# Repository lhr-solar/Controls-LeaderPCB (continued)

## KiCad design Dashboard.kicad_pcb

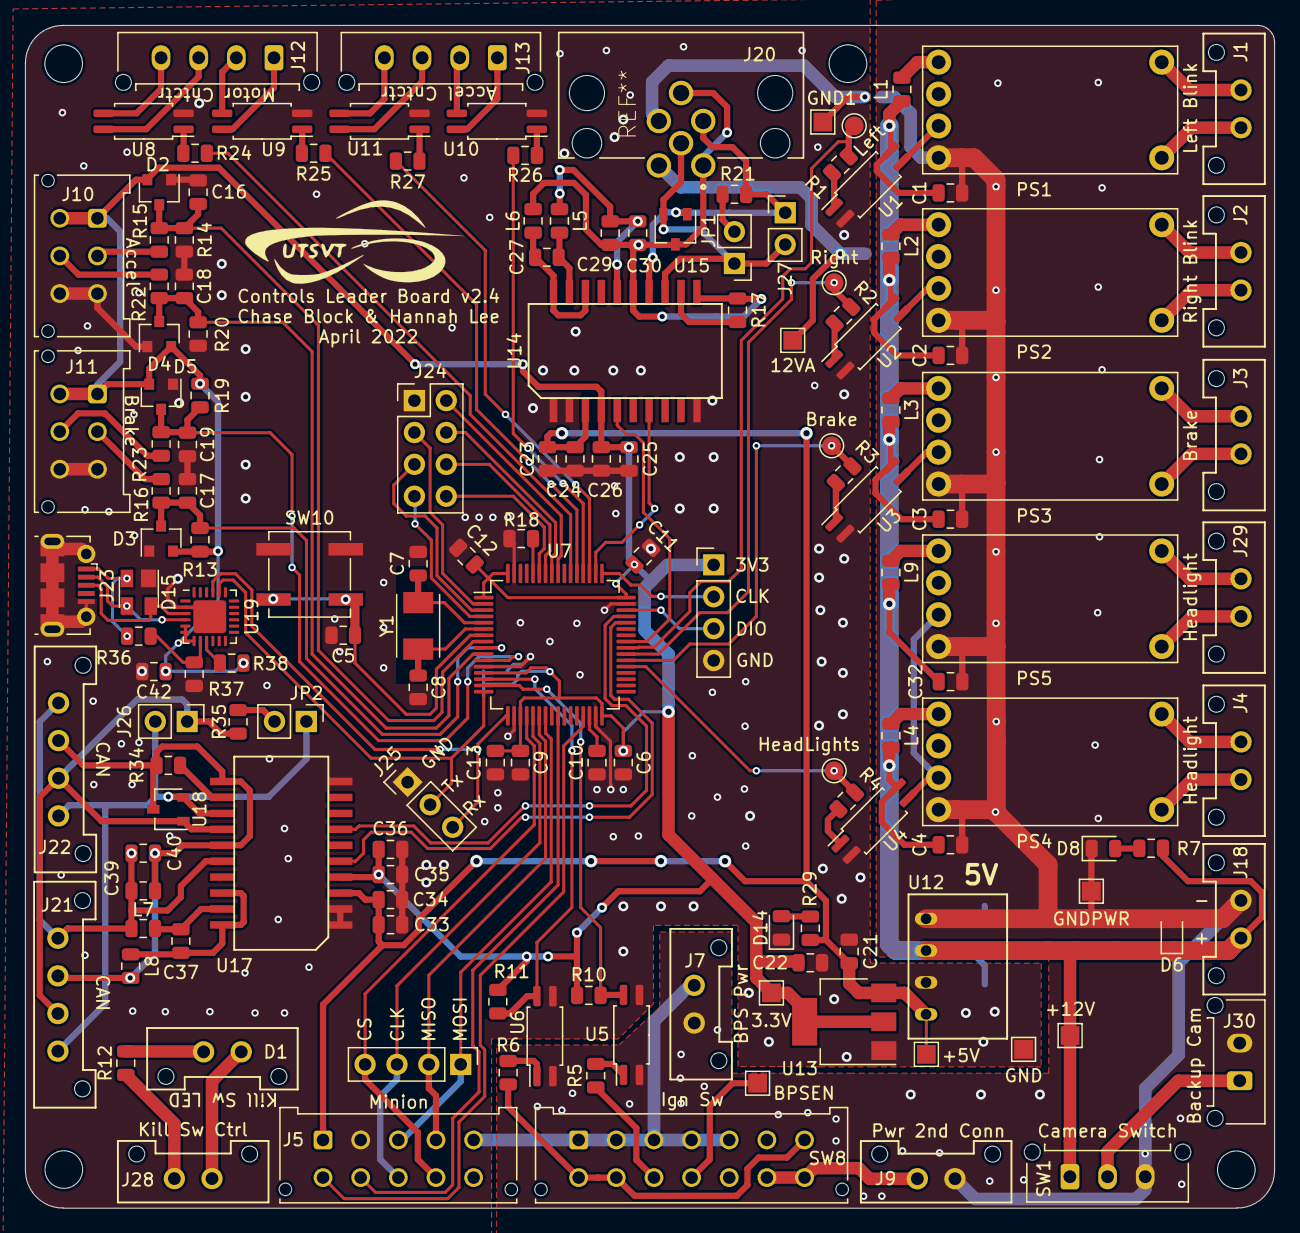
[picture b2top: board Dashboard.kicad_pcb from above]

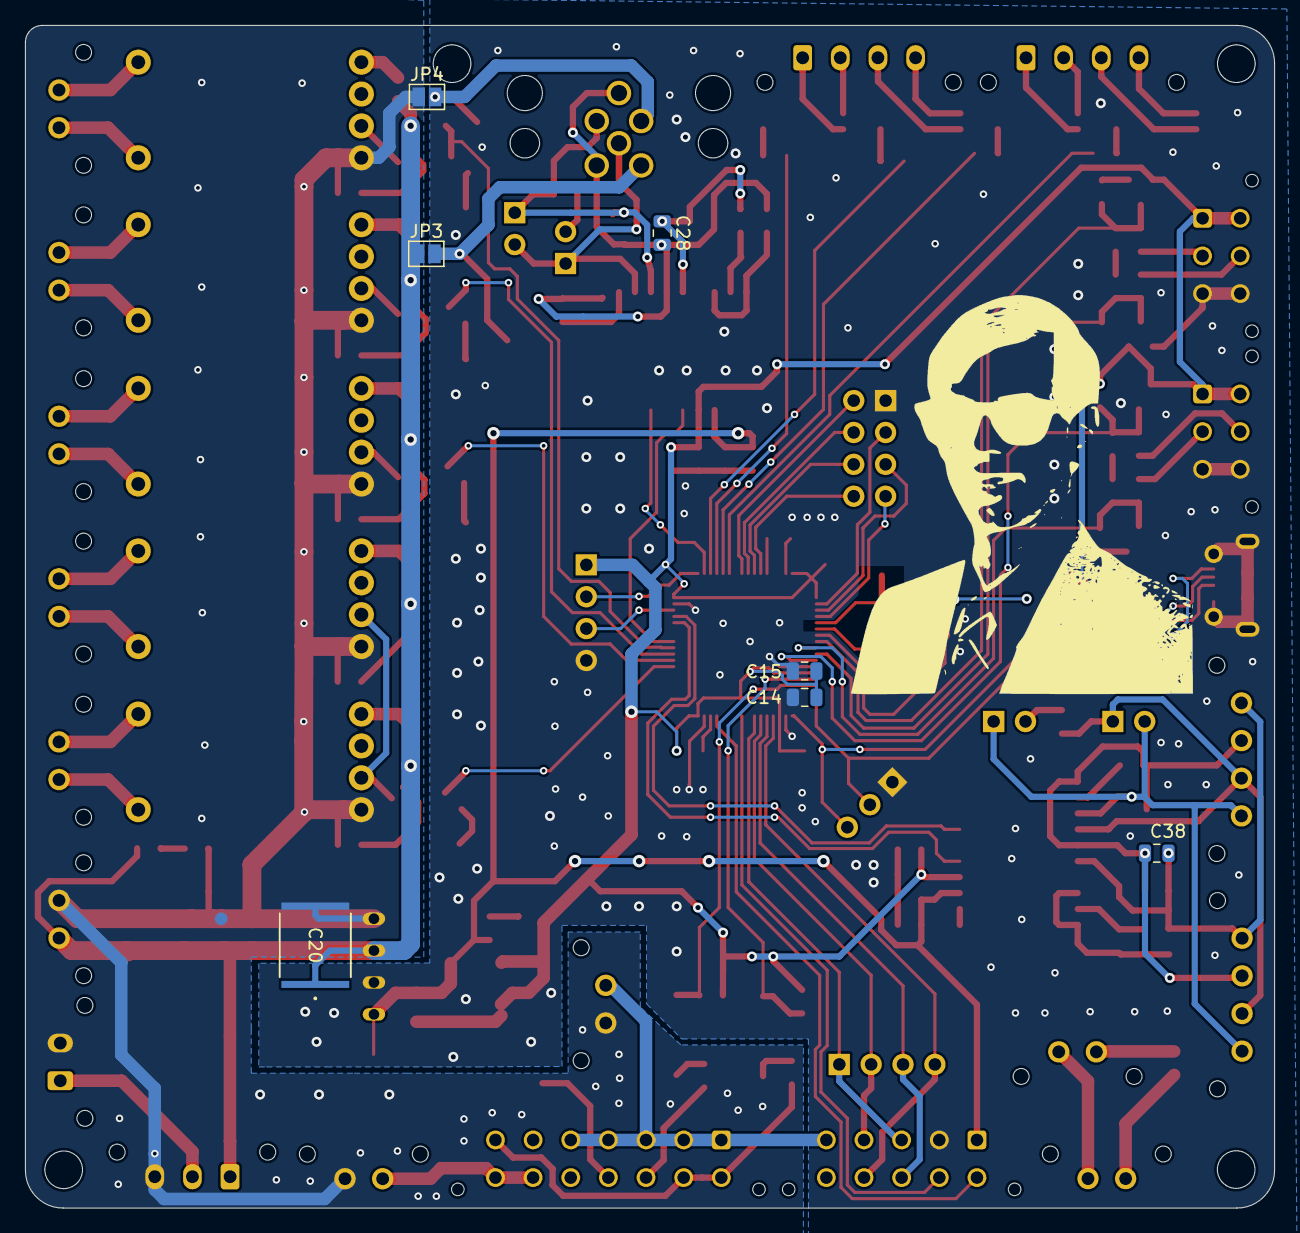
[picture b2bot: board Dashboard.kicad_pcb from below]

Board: 2 copper layers, 99.5 x 94.2 mm, 164 parts (9 on the bottom side), 120 nets.

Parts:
C1, C2, C3, C4, C32: 1u; C_0805_2012Metric
C5, C6, C9, C11, C12, C14: 100nF; C_0805_2012Metric
C7, C8: 12pF; C_0805_2012Metric
C10, C13, C41: 4.7uF; C_0805_2012Metric
C15: 1uF; C_0805_2012Metric
C16, C17, C18, C19, C24, C25, C29, C34, C35, C39, C42: 0.1uF; C_0805_2012Metric
C20: 10u; C_2220_5750Metric
C21, C22: 10u; C_0805_2012Metric
C23, C28, C33, C38: 10uF; C_0805_2012Metric
C26, C30, C36, C40: 0.01uF; C_0805_2012Metric
C27, C37: 0.22uF; C_0805_2012Metric
D1: KILL_SW_LED; Molex_MicroFit3.0_1x2xP3.00mm_PolarizingPeg_Vertical
D2, D3, D4, D5: BAS70-04; SOT-23
D6: TVS; D_SOD-323
D8, D14: PowerOn; LED_0805_2012Metric
D15: SP0503BAHT; SOT-143
H1, H2, H3, H4: MountingHole; MountingHole_3mm
J1: Left_Signal; Molex_MicroFit3.0_1x2xP3.00mm_PolarizingPeg_Vertical
J2: Right_Signal; Molex_MicroFit3.0_1x2xP3.00mm_PolarizingPeg_Vertical
J3: Brake Light; Molex_MicroFit3.0_1x2xP3.00mm_PolarizingPeg_Vertical
J4, J29: Headlight; Molex_MicroFit3.0_1x2xP3.00mm_PolarizingPeg_Vertical
J5: MinionConn; Molex_Micro-Fit_3.0_43045-1012_2x05_P3.00mm_Vertical
J6: SPI; PinHeader_1x04_P2.54mm_Vertical
J7: BPS_PWR_OUT; Molex_MicroFit3.0_1x2xP3.00mm_PolarizingPeg_Vertical
J8: SWD; PinHeader_1x04_P2.54mm_Vertical
J9: POW_2ND_CONN; Molex_MicroFit3.0_1x2xP3.00mm_PolarizingPeg_Vertical
J10, J11: Conn_02x03_Top_Bottom; Molex_Micro-Fit_3.0_43045-0612_2x03_P3.00mm_Vertical
J12, J13: Conn_01x04; Molex_Micro-Fit_3.0_43650-0415_1x04_P3.00mm_Vertical
J18: PowerConn; Molex_MicroFit3.0_1x2xP3.00mm_PolarizingPeg_Vertical
J20: MotorCANConnector; TE_4-2172079-2
J21: CAN_IN; Molex_MicroFit3.0_1x4xP3.00mm_PolarizingPeg_Vertical
J22: CAN_OUT; Molex_MicroFit3.0_1x4xP3.00mm_PolarizingPeg_Vertical
J23: USB_B_Micro; USB_Micro-B_Molex-105017-0001
J24: ExtraGPIO_Conn; PinHeader_2x04_P2.54mm_Vertical
J25: UART_TP; PinHeader_1x03_P2.54mm_Vertical
J26, J27: CAN_TP; PinHeader_1x02_P2.54mm_Vertical
J28: KILL_SW_IND; Molex_MicroFit3.0_1x2xP3.00mm_PolarizingPeg_Vertical
J30: Backup Camera; Molex_Micro-Fit_3.0_43650-0215_1x02_P3.00mm_Vertical
JP1, JP2: Termination Resistors; PinHeader_1x02_P2.54mm_Vertical
JP3, JP4: Jumper_2_Bridged; SolderJumper-2_P1.3mm_Open_Pad1.0x1.5mm
L1, L2, L3, L4, L9: 22u; L_0805_2012Metric
L5, L6, L7, L8: 2kH; L_0805_2012Metric
LOGO1: Dr. Hallock; Hallock_Image
LOGO2: UTSVT; UTSVT_Logo_Symbol
PS1, PS2, PS3, PS4, PS5: RCD-24
R1, R2, R3, R4: 105; R_0805_2012Metric
R5, R6: 510; R_0805_2012Metric
R7, R29: 1.5k; R_0805_2012Metric
R10, R11: 4.9k; R_0805_2012Metric
R12: 1.2k; R_0805_2012Metric
R13, R14, R19, R20: 5.1k; R_0805_2012Metric
R15, R16, R18, R22, R23: 10k; R_0805_2012Metric
R17, R34: 0; R_0805_2012Metric
R21, R35: 120; R_0805_2012Metric
R24, R25, R26, R27: 105R; R_0805_2012Metric
R36: 22.1k; R_0805_2012Metric
R37: 47.5k; R_0805_2012Metric
R38: 1k; R_0805_2012Metric
SW1: BACKUP_SW; Molex_Micro-Fit_3.0_43650-0315_1x03_P3.00mm_Vertical
SW8: SW_Rotary2x6; Molex_Micro-Fit_3.0_43045-1412_2x07_P3.00mm_Vertical
SW10: RESET; SW_SPST_B3SL-1002P
TP1: LEFT_BLINK; TestPoint_Pad_D1.5mm
TP2: +12V_TP; TestPoint_Pad_1.5x1.5mm
TP3: GNDPWR_TP; TestPoint_Pad_1.5x1.5mm
TP4: +5V_TP; TestPoint_Pad_1.5x1.5mm
TP5: GND_TP; TestPoint_Pad_1.5x1.5mm
TP6: +3.3V_TP; TestPoint_Pad_1.5x1.5mm
TP7: RIGHT_BLINK; TestPoint_Pad_D1.5mm
TP8: BK_LIGHT; TestPoint_Pad_D1.5mm
TP9: Headlight_PWR; TestPoint_Pad_D1.5mm
TP10: POWER; TestPoint_Pad_1.5x1.5mm
TP13: +12VA_TP; TestPoint_Pad_1.5x1.5mm
TP14: GND1_TP; TestPoint_Pad_1.5x1.5mm
U1, U2, U3, U4, U5, U6, U8, U9, U10, U11: EL3H7; SOP-4_4.4x2.6mm_P1.27mm
U7: STM32F413RHTx; LQFP-64_10x10mm_P0.5mm
U12: RI3-1205S; RI3_DC_Converter
U13: NCP1117-3.3_SOT223; SOT-223-3_TabPin2
U14, U17: ADM3055E; SOIC-20W_7.5x15.4mm_Pitch1.27mm
U15, U18: CDSOT23-T24CAN; SOT-23W
U19: CP2102N-A01-GQFN24; QFN-24-1EP_4x4mm_P0.5mm_EP2.6x2.6mm
Y1: Crystal; Crystal_SMD_TXC_7A-2Pin_5x3.2mm

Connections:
+3V3: C6.1, C9.1, C11.1, C12.1, C13.1, C14.1, C15.1, C22.1, C25.1, C26.1, C35.1, C36.1, C41.1, C42.1, D2.2, D3.2, D4.2, D5.2, J8.1, J10.1, J10.4, J11.1, J11.4, R10.1, R11.1, R13.1, R19.1, R38.1, TP6.1, U7.1 (VBAT), U7.13 (VDDA), U7.19 (VDD), U7.32 (VDD), U7.48 (VDD), U7.64 (VDD), U13.2 (VO), U14.4 (V_IO), U17.4 (V_IO), U19.5 (VIO), U19.6 (VDD), U19.7 (REGIN)
+5V: C21.1, C23.1, C24.1, C33.1, C34.1, J5.1, R29.1, TP4.1, U12.4 (+Vout), U13.3 (VI), U14.3 (V_In), U17.3 (V_In)
+12V: C1.2, C2.2, C3.2, C4.2, C20.1, C32.2, D6.1 (K), J18.1, JP3.1 (A), L1.2, L2.2, L3.2, L4.2, L9.2, R7.1, SW1.1 (A), TP2.1, U1.4, U2.4, U3.4, U4.4, U12.2 (+Vin)
+12VA: J20.2 (+12V), JP3.2 (B), TP13.1
/A_CNCTR: R26.2, U7.52 (PC11)
/A_PRCHG: R27.2, U7.51 (PC10)
/Accel_Pot: C16.1, D2.3, R14.1, R15.2, U7.8 (PC0)
/Accel_Pot2: C18.1, D4.3, R20.1, R22.2, U7.10 (PC2)
/BK_LIGHT: R3.2, TP8.1, U7.38 (PC7)
/BPS_PWR: J5.5, J7.1, SW8.1, SW8.2, SW8.3, SW8.4, SW8.5
/Brake_Pot: C17.1, D3.3, R13.2, R16.2, U7.9 (PC1)
/Brake_Pot2: C19.1, D5.3, R19.2, R23.2, U7.11 (PC3)
/CAN_Rx: U7.44 (PA11), U17.5 (RX)
/CAN_Tx: U7.45 (PA12), U17.7 (TX)
/CLK: J5.8, J6.3, U7.21 (PA5)
/CS: J5.9, J6.4, U7.20 (PA4)
/Car_CAN/CAN_H: J21.3, J22.3, J26.1, R35.2, U17.14 (CAN_H), U18.1 (CAN_H)
/Car_CAN/CAN_L: J21.4, J22.4, J26.2, JP2.1, U17.13 (CAN_L), U18.2 (CAN_L)
/Car_CAN/RSlope: R34.1, U17.12 (RS)
/Car_CAN/TERM_H: JP2.2, R35.1
/Headlight_ON: R4.2, TP9.1, U7.37 (PC6)
/IG1: R10.2, U5.4, U7.15 (PA1)
/IG2: R11.2, U6.4, U7.14 (PA0)
/LEFT_BLINK: R1.2, TP1.1, U7.40 (PC9)
/MISO: J5.4, J6.2, U7.22 (PA6)
/MOSI: J5.3, J6.1, U7.23 (PA7)
/M_CNCTR: R25.2, U7.53 (PC12)
/M_PRCHG: R24.2, U7.54 (PD2)
/MotorCAN_Rx: U7.41 (PA8), U14.5 (RX)
/MotorCAN_Tx: U7.50 (PA15), U14.7 (TX)
/Motor_CAN/CAN_H: J20.4 (CAN_H), J27.1, R21.2, U14.14 (CAN_H), U15.1 (CAN_H)
/Motor_CAN/CAN_L: J20.5 (CAN_L), J27.2, JP1.1, U14.13 (CAN_L), U15.2 (CAN_L)
/Motor_CAN/RSlope: R17.1, U14.12 (RS)
/Motor_CAN/TERM_H: JP1.2, R21.1
/NRST: C5.1, SW10.2 (B), U7.7 (NRST)
/PB4: J24.2, U7.56 (PB4)
/PB5: J24.4, U7.57 (PB5)
/PB6: J24.6, U7.58 (PB6)
/PB7: J24.8, U7.59 (PB7)
/PC13: J24.3, U7.2 (PC13)
/PC14: J24.5, U7.3 (PC14)
/PC15: J24.7, U7.4 (PC15)
/RIGHT_BLINK: R2.2, TP7.1, U7.39 (PC8)
/SWCLK: J8.2, U7.49 (PA14)
/SWDIO: J8.3, U7.46 (PA13)
/UART2_Rx: J25.3, U7.17 (PA3), U19.21 (TXD)
/UART2_Tx: J25.2, U7.16 (PA2), U19.20 (RXD)
/UART3_Rx: J5.7, U7.25 (PC5)
/UART3_Tx: J5.6, U7.29 (PB10)
GND: C5.2, C6.2, C7.2, C8.2, C9.2, C10.1, C11.2, C12.2, C13.2, C14.2, C15.2, C16.2, C17.2, C18.2, C19.2, C21.2, C22.2, C23.2, C24.2, C25.2, C26.2, C33.2, C34.2, C35.2, C36.2, C41.2, C42.2, D2.1, D3.1, D4.1, D5.1, D14.1 (K), D15.1 (A), J5.2, J8.4, J10.3, J10.6, J11.3, J11.6, J23.5 (GND), J23.6 (Shield), J24.1, J25.1, R14.2, R18.2, R20.2, R37.2, SW10.1 (A), TP5.1, U1.2, U2.2, U3.2, U4.2, U5.3, U6.3, U7.12 (VSSA), U7.18 (VSS), U7.31 (VSS), U7.47 (VSS), U7.63 (VSS), U8.2, U9.2, U10.2, U11.2, U12.3 (-Vout), U13.1 (GND), U14.1 (GND_In), U14.2 (GND_In), U14.10 (GND_In), U17.1 (GND_In), U17.2 (GND_In), U17.10 (GND_In), U19.2 (GND), U19.25 (GND)
GND1: J20.3 (GND), JP4.2 (B), TP14.1
GNDPWR: C1.1, C2.1, C3.1, C4.1, C20.2, C32.1, D6.2 (A), D8.1 (K), J7.2, J9.2, J18.2, J30.2, JP4.1 (A), PS1.4 (GND), PS2.4 (GND), PS3.4 (GND), PS4.4 (GND), PS5.4 (GND), SW1.3 (C), TP3.1, U5.2, U6.2, U12.1 (-Vin)
unnamed: C7.1, U7.5 (PH0), Y1.2
unnamed: C8.1, U7.6 (PH1), Y1.1
unnamed: C10.2, U7.30 (VCAP_1)
unnamed: C27.1, L5.2, U14.19 (V_ISO_Out)
unnamed: C27.2, L6.2, U14.18 (GND_ISO_Out), U14.20 (GND_ISO_Out)
unnamed: C28.1, C29.1, C30.1, L5.1, U14.16 (V_ISO_In)
unnamed: C28.2, C29.2, C30.2, J20.1 (Shield_GND), J20.S1 (SHIELD), L6.1, R17.2, U14.11 (GND_ISO_In), U14.15 (GND_ISO_In), U15.3 (GND)
unnamed: C37.1, L7.2, U17.19 (V_ISO_Out)
unnamed: C37.2, L8.2, U17.18 (GND_ISO_Out), U17.20 (GND_ISO_Out)
unnamed: C38.1, C39.1, C40.1, J21.1, J22.1, L7.1, U17.16 (V_ISO_In)
unnamed: C38.2, C39.2, C40.2, J21.2, J22.2, L8.1, R34.2, U17.11 (GND_ISO_In), U17.15 (GND_ISO_In), U18.3 (GND)
unnamed: D1.1 (K), J28.2
unnamed: D1.2 (A), R12.2
unnamed: D8.2 (A), R7.2
unnamed: D14.2 (A), R29.2
unnamed: D15.2 (K), J23.1 (VBUS), R36.2
unnamed: D15.3 (K), J23.2 (D-), U19.4 (D-)
unnamed: D15.4 (K), J23.3 (D+), U19.3 (D+)
unnamed: J1.1, PS1.5 (-Vout)
unnamed: J1.2, PS1.6 (+Vout)
unnamed: J2.1, PS2.5 (-Vout)
unnamed: J2.2, PS2.6 (+Vout)
unnamed: J3.1, PS3.5 (-Vout)
unnamed: J3.2, PS3.6 (+Vout)
unnamed: J4.1, PS4.5 (-Vout)
unnamed: J4.2, PS4.6 (+Vout)
unnamed: J9.1, SW8.13, SW8.14
unnamed: J28.1, R12.1
unnamed: J29.1, PS5.5 (-Vout)
unnamed: J29.2, PS5.6 (+Vout)
unnamed: J30.1, SW1.2 (B)
unnamed: L1.1, PS1.1 (+Vin)
unnamed: L2.1, PS2.1 (+Vin)
unnamed: L3.1, PS3.1 (+Vin)
unnamed: L4.1, PS4.1 (+Vin)
unnamed: L9.1, PS5.1 (+Vin)
unnamed: PS1.3 (PWM), U1.3
unnamed: PS2.3 (PWM), U2.3
unnamed: PS3.3 (PWM), U3.3
unnamed: PS4.3 (PWM), PS5.3 (PWM), U4.3
unnamed: R1.1, U1.1
unnamed: R2.1, U2.1
unnamed: R3.1, U3.1
unnamed: R4.1, U4.1
unnamed: R5.1, SW8.10
unnamed: R5.2, U5.1
unnamed: R6.1, SW8.7, SW8.8, SW8.9
unnamed: R6.2, U6.1
unnamed: J10.2, R15.1
unnamed: J11.2, R16.1
unnamed: R18.1, U7.60 (BOOT0)
unnamed: J10.5, R22.1
unnamed: J11.5, R23.1
unnamed: R24.1, U8.1
unnamed: R25.1, U9.1
unnamed: R26.1, U10.1
unnamed: R27.1, U11.1
unnamed: R36.1, R37.1, U19.8 (VBUS)
unnamed: R38.2, U19.9 (~RSTb)
unnamed: SW8.11, TP10.1
unnamed: J12.4, U8.3
unnamed: J12.3, U8.4
unnamed: J12.2, U9.3
unnamed: J12.1, U9.4
unnamed: J13.2, U10.3
unnamed: J13.1, U10.4
unnamed: J13.4, U11.3
unnamed: J13.3, U11.4

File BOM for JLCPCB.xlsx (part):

Comment |  |  | Designator |  |  |  | Footprint |  |  |  |  |  |  | JLCPCB Part # P/N |  |  | Stock in jlc
1u |  |  | C1 |  |  |  | Capacitor_SMD:C_0805_2012Metric |  |  |  |  |  |  | C28323 |  |  | 647623
1u |  |  | C2 |  |  |  | Capacitor_SMD:C_0805_2012Metric |  |  |  |  |  |  | C28323 |  |  | 647623
1u |  |  | C3 |  |  |  | Capacitor_SMD:C_0805_2012Metric |  |  |  |  |  |  | C28323 |  |  | 647623
1u |  |  | C4 |  |  |  | Capacitor_SMD:C_0805_2012Metric |  |  |  |  |  |  | C28323 |  |  | 647623
1u |  |  | C32 |  |  |  | Capacitor_SMD:C_0805_2012Metric |  |  |  |  |  |  | C28323 |  |  | 647623
100nF |  |  | C5 |  |  |  | Capacitor_SMD:C_0805_2012Metric |  |  |  |  |  |  | C49678 |  |  | 6507420
100nF |  |  | C6 |  |  |  | Capacitor_SMD:C_0805_2012Metric |  |  |  |  |  |  | C49678 |  |  | 6507420
100nF |  |  | C9 |  |  |  | Capacitor_SMD:C_0805_2012Metric |  |  |  |  |  |  | C49678 |  |  | 6507420
100nF |  |  | C11 |  |  |  | Capacitor_SMD:C_0805_2012Metric |  |  |  |  |  |  | C49678 |  |  | 6507420
100nF |  |  | C12 |  |  |  | Capacitor_SMD:C_0805_2012Metric |  |  |  |  |  |  | C49678 |  |  | 6507420
100nF |  |  | C16 |  |  |  | Capacitor_SMD:C_0805_2012Metric |  |  |  |  |  |  | C49678 |  |  | 6507420
100nF |  |  | C17 |  |  |  | Capacitor_SMD:C_0805_2012Metric |  |  |  |  |  |  | C49678 |  |  | 6507420
100nF |  |  | C18 |  |  |  | Capacitor_SMD:C_0805_2012Metric |  |  |  |  |  |  | C49678 |  |  | 6507420
100nF |  |  | C19 |  |  |  | Capacitor_SMD:C_0805_2012Metric |  |  |  |  |  |  | C49678 |  |  | 6507420
100nF |  |  | C24 |  |  |  | Capacitor_SMD:C_0805_2012Metric |  |  |  |  |  |  | C49678 |  |  | 6507420
100nF |  |  | C25 |  |  |  | Capacitor_SMD:C_0805_2012Metric |  |  |  |  |  |  | C49678 |  |  | 6507420
100nF |  |  | C29 |  |  |  | Capacitor_SMD:C_0805_2012Metric |  |  |  |  |  |  | C49678 |  |  | 6507420
100nF |  |  | C34 |  |  |  | Capacitor_SMD:C_0805_2012Metric |  |  |  |  |  |  | C49678 |  |  | 6507420
100nF |  |  | C35 |  |  |  | Capacitor_SMD:C_0805_2012Metric |  |  |  |  |  |  | C49678 |  |  | 6507420
100nF |  |  | C39 |  |  |  | Capacitor_SMD:C_0805_2012Metric |  |  |  |  |  |  | C49678 |  |  | 6507420
100nF |  |  | C42 |  |  |  | Capacitor_SMD:C_0805_2012Metric |  |  |  |  |  |  | C49678 |  |  | 6507420
12pF |  |  | C7 |  |  |  | Capacitor_SMD:C_0805_2012Metric |  |  |  |  |  |  | C376863 |  |  | 3913
12pF |  |  | C8 |  |  |  | Capacitor_SMD:C_0805_2012Metric |  |  |  |  |  |  | C376863 |  |  | 3913
4.7uF |  |  | C10 |  |  |  | Capacitor_SMD:C_0805_2012Metric |  |  |  |  |  |  | C1779 |  |  | 2094551
4.7uF |  |  | C13 |  |  |  | Capacitor_SMD:C_0805_2012Metric |  |  |  |  |  |  | C1779 |  |  | 2094551
4.7uF |  |  | C41 |  |  |  | Capacitor_SMD:C_0805_2012Metric |  |  |  |  |  |  | C1779 |  |  | 2094551
10u |  |  | C20 |  |  |  | Capacitor_SMD:C_0805_2012Metric |  |  |  |  |  |  | C15850 |  |  | 5148770
10u |  |  | C21 |  |  |  | Capacitor_SMD:C_0805_2012Metric |  |  |  |  |  |  | C15850 |  |  | 5148770
10u |  |  | C22 |  |  |  | Capacitor_SMD:C_0805_2012Metric |  |  |  |  |  |  | C15850 |  |  | 5148770
10u |  |  | C23 |  |  |  | Capacitor_SMD:C_0805_2012Metric |  |  |  |  |  |  | C15850 |  |  | 5148770
10u |  |  | C28 |  |  |  | Capacitor_SMD:C_0805_2012Metric |  |  |  |  |  |  | C15850 |  |  | 5148770
10u |  |  | C33 |  |  |  | Capacitor_SMD:C_0805_2012Metric |  |  |  |  |  |  | C15850 |  |  | 5148770
10u |  |  | C38 |  |  |  | Capacitor_SMD:C_0805_2012Metric |  |  |  |  |  |  | C15850 |  |  | 5148770
0.01uF |  |  | C26 |  |  |  | Capacitor_SMD:C_0805_2012Metric |  |  |  |  |  |  | C1710 |  |  | 518880
0.01uF |  |  | C30 |  |  |  | Capacitor_SMD:C_0805_2012Metric |  |  |  |  |  |  | C1710 |  |  | 518880
0.01uF |  |  | C36 |  |  |  | Capacitor_SMD:C_0805_2012Metric |  |  |  |  |  |  | C1710 |  |  | 518880
0.01uF |  |  | C40 |  |  |  | Capacitor_SMD:C_0805_2012Metric |  |  |  |  |  |  | C1710 |  |  | 518880
0.22uF |  |  | C27 |  |  |  | Capacitor_SMD:C_0805_2012Metric |  |  |  |  |  |  | C5378 |  |  | 135203
0.22uF |  |  | C37 |  |  |  | Capacitor_SMD:C_0805_2012Metric |  |  |  |  |  |  | C5378 |  |  | 135203
BAS70-04 |  |  | D2 |  |  |  | Package_TO_SOT_SMD:SOT-23 |  |  |  |  |  |  | C5184402 |  |  | 24530
BAS70-04 |  |  | D3 |  |  |  | Package_TO_SOT_SMD:SOT-23 |  |  |  |  |  |  | C5184402 |  |  | 24530
BAS70-04 |  |  | D4 |  |  |  | Package_TO_SOT_SMD:SOT-23 |  |  |  |  |  |  | C5184402 |  |  | 24530
BAS70-04 |  |  | D5 |  |  |  | Package_TO_SOT_SMD:SOT-23 |  |  |  |  |  |  | C5184402 |  |  | 24530
TVS |  |  | D6 |  |  |  | Diode_SMD:D_SOD-323 |  |  |  |  |  |  | C5190176 |  |  | 833
PowerOn |  |  | D8 |  |  |  | LED_SMD:LED_0805_2012Metric |  |  |  |  |  |  | C5366381 |  |  | 3139
PowerOn |  |  | D14 |  |  |  | LED_SMD:LED_0805_2012Metric |  |  |  |  |  |  | C5366381 |  |  | 3139
SP0503BAHT |  |  | D15 |  |  |  | Package_TO_SOT_SMD:SOT-143 |  |  |  |  |  |  | C3040626 |  |  | 120289
110 |  |  | R1 |  |  |  | Resistor_SMD:R_0805_2012Metric |  |  |  |  |  |  | C2933517 |  |  | 844
110 |  |  | R2 |  |  |  | Resistor_SMD:R_0805_2012Metric |  |  |  |  |  |  | C2933517 |  |  | 844
110 |  |  | R3 |  |  |  | Resistor_SMD:R_0805_2012Metric |  |  |  |  |  |  | C2933517 |  |  | 844
110 |  |  | R4 |  |  |  | Resistor_SMD:R_0805_2012Metric |  |  |  |  |  |  | C2933517 |  |  | 844
110 |  |  | R24 |  |  |  | Resistor_SMD:R_0805_2012Metric |  |  |  |  |  |  | C2933517 |  |  | 844
110 |  |  | R25 |  |  |  | Resistor_SMD:R_0805_2012Metric |  |  |  |  |  |  | C2933517 |  |  | 844
110 |  |  | R26 |  |  |  | Resistor_SMD:R_0805_2012Metric |  |  |  |  |  |  | C2933517 |  |  | 844
110 |  |  | R27 |  |  |  | Resistor_SMD:R_0805_2012Metric |  |  |  |  |  |  | C2933517 |  |  | 844
510 |  |  | R5 |  |  |  | Resistor_SMD:R_0805_2012Metric |  |  |  |  |  |  | C2828857 |  |  | 964
510 |  |  | R6 |  |  |  | Resistor_SMD:R_0805_2012Metric |  |  |  |  |  |  | C2828857 |  |  | 964
1.5k |  |  | R7 |  |  |  | Resistor_SMD:R_0805_2012Metric |  |  |  |  |  |  | C4310 |  |  | 436191
1.5k |  |  | R29 |  |  |  | Resistor_SMD:R_0805_2012Metric |  |  |  |  |  |  | C4310 |  |  | 436191
5k |  |  | R10 |  |  |  | Resistor_SMD:R_0805_2012Metric |  |  |  |  |  |  | C2828700 |  |  | 3316
5k |  |  | R11 |  |  |  | Resistor_SMD:R_0805_2012Metric |  |  |  |  |  |  | C2828700 |  |  | 3316
5k |  |  | R13 |  |  |  | Resistor_SMD:R_0805_2012Metric |  |  |  |  |  |  | C2828700 |  |  | 3316
5k |  |  | R14 |  |  |  | Resistor_SMD:R_0805_2012Metric |  |  |  |  |  |  | C2828700 |  |  | 3316
5k |  |  | R19 |  |  |  | Resistor_SMD:R_0805_2012Metric |  |  |  |  |  |  | C2828700 |  |  | 3316
5k |  |  | R20 |  |  |  | Resistor_SMD:R_0805_2012Metric |  |  |  |  |  |  | C2828700 |  |  | 3316
1.2k |  |  | R12 |  |  |  | Resistor_SMD:R_0805_2012Metric |  |  |  |  |  |  | C17379 |  |  | 163751
10k |  |  | R15 |  |  |  | Resistor_SMD:R_0805_2012Metric |  |  |  |  |  |  | C17414 |  |  | 18834045
10k |  |  | R16 |  |  |  | Resistor_SMD:R_0805_2012Metric |  |  |  |  |  |  | C17414 |  |  | 18834045
10k |  |  | R18 |  |  |  | Resistor_SMD:R_0805_2012Metric |  |  |  |  |  |  | C17414 |  |  | 18834045
10k |  |  | R22 |  |  |  | Resistor_SMD:R_0805_2012Metric |  |  |  |  |  |  | C17414 |  |  | 18834045
10k |  |  | R23 |  |  |  | Resistor_SMD:R_0805_2012Metric |  |  |  |  |  |  | C17414 |  |  | 18834045
0 |  |  | R17 |  |  |  | Resistor_SMD:R_0805_2012Metric |  |  |  |  |  |  | C17477 |  |  | 1157685
0 |  |  | R34 |  |  |  | Resistor_SMD:R_0805_2012Metric |  |  |  |  |  |  | C17477 |  |  | 1157685
120 |  |  | R21 |  |  |  | Resistor_SMD:R_0805_2012Metric |  |  |  |  |  |  | C17437 |  |  | 303844
120 |  |  | R35 |  |  |  | Resistor_SMD:R_0805_2012Metric |  |  |  |  |  |  | C17437 |  |  | 303844
22.1k |  |  | R36 |  |  |  | Resistor_SMD:R_0805_2012Metric |  |  |  |  |  |  | C17552 |  |  | 50
47.5k |  |  | R37 |  |  |  | Resistor_SMD:R_0805_2012Metric |  |  |  |  |  |  | C26011 |  |  | 2177
1k |  |  | R38 |  |  |  | Resistor_SMD:R_0805_2012Metric |  |  |  |  |  |  | C17513 |  |  | 9841243
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
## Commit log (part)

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2020-08-02 Set up for own repository
2020-08-08 Updates submodule commit ID
2020-08-08 Updates dashboard project to most recent version
2020-08-11 Adds files to a new branch
2020-09-12 Updates common
2020-09-12 Edits schematic to make turn lights software controlled
2020-09-12 Updates PCB to add changes from the schematic
2020-09-12 Updates common submodule
2020-09-19 Organizes the schematic into hierarchical sheets
2020-09-19 Generates netlist and updates PCB components
2020-09-27 Adds components for the shift register and lays out modularized components
2020-09-27 Lays out PCB for Controls leader board
2020-10-01 Adds SPI header to test
2020-10-01 Makes all traces .25 mm
2020-10-03 Labels sections and fixes DRC errors
2020-10-03 Adds QuAC
2020-10-03 Adds labels to some connectors and edits layout to meet 0,2mm pad to trace clearance
2020-10-03 Finishes label and redesigns emergency switch/error light circuitry
2020-10-03 Adds connector for power secondary board
2020-10-09 Makes the 12V and GNDPWR traces bigger
2020-10-09 Extends the GND plane to under the potentiometers
2020-10-09 Creates and then removes Gerbers
2020-10-10 Add STEP file
2020-12-12 Creates pdf of schematic
2020-12-19 Adds BPSPWR as a connection to the minion board and then fixes labels
2021-01-10 Changes display power to 5V, puts fault LED on back, and adds gerbers
2021-01-23 Adds gerbers
2021-01-23 Updates Controls Leader PCB
2021-02-06 3D models and resized rotary switch
2021-02-06 Cleans up folder and updates gerbers
2021-10-02 USB Tx/Rx, Crystal Keepout, 12V Separation, Can2-Can3, Motor CAN bus labels, Power Input Protection Circuitry
2021-10-03 Connects pots to ADC pins and removes JTAG connections
2021-10-03 Flips exterior lights polarity on the connectors
2021-10-04 Updates gerbers and version number
2021-11-06 removes the isp
2021-11-06 removes isp
2021-11-14 Changes the layout of the board, adds resistors for ignition switch, and gives motar can isolated +12v, still need to change resistor value for the isolated +12v(didnt remember how to find the value)
2021-11-16 Cleans up some of the traces in the power section
2021-12-07 Updates gerbers and new controls leader
2022-02-21 Redo the board layout to be more compact.
    IMPORTANT: as of this moment, this is only a proposal for
    a new design, and the team has *not* determined whether
    this is necessary.
    This addresses some issues that I have had with the design
    of the Controls Leader board:
    - It is too bulky, and would be difficult to mount
2022-04-02 Remove 12V isolator, swap CAN connector pins, etc.
2022-04-02 Release v2.4 and gerbers
2023-10-13 Initialized Controls Daughter PCB
2023-10-13 Removed .lck file
2023-10-13 updated gitignore
2023-10-13 added UTSVT submodule
2023-10-14 changed resistor values, updated footprints
2023-10-21 Added drived fan circuitry
2023-10-21 Added resistor to fan isolator, fixed ERC errors and warnings
2023-10-21 added version history text
2023-10-21 changed labels for some connectors
2023-10-28 renamed root directory
2023-10-28 fixed renaming, no longer has duplicated project
2023-10-28 lower power optocouplers now used for lights and fans, updated version history
2023-10-28 changed version history
2023-11-04 Added flyback diodes to fan connectors
2023-11-04 Removed ignition switch connection and redid ignition signals
2023-11-04 Layed out SOM boot-hat connections
2023-11-04 Removed neutral section's debouncing circuitry and connections
2023-11-04 Added test points
2023-11-04 Adjusted & added footprints, several minor changes
2023-11-04 Changed optocoupler resistor values, updated Mouser PNs
2023-11-04 Uploaded image for ReadME
2023-11-04 Changed image file name
2023-11-04 Updated ReadME image
2023-12-02 Switch ignition switch signal's resistor from pull-up to pull-down
2023-12-02 Added I2C GPIO expander to reduce GPIO pins from LeaderSOM and replace 555 timer circuit. Adjusted ignition switch signals.
2024-01-07 Added debouncing, bypass caps, pull up and down resistors, and current limiting resistors. Removed some TPs.
2024-01-17 Organized schematic, removed fan MOSFET
2024-01-17 assigned footprints
2024-01-17 organized schematic, changed resistor values, moved ignition signals to IC
2024-01-17 added second fan FET back
2024-01-18 fixed library issues
2024-01-18 Organized schematic, added reset function to extender, changed footprints
2024-01-20 added notes section to bottom of sheets
2024-01-20 renamed Dash to Controls-Leader
2024-01-20 Added to notes and changed resistor values
2024-01-20 renamed Dash to Controls-Leader (#22)
    * renamed Dash to Controls-Leader
    * :)
2024-04-06 added jlc bom assembly excel file
2024-04-13 ignore .lck files and deleted lck files
2024-04-13 added cpl file (positions.csv), updated BOM excel sheet, turned gerbers into zip file
2024-04-13 moved positions out of a separate folder
2024-04-13 updated resistor parts (510 and 5.1k to 5k)
2024-04-13 rename excel sheet
2024-04-17 updated positions.csv
2024-06-05 fixed BOM
2024-06-05 fixed gitignore
2024-06-05 ahhhhhhhhhhhhhhhhhhhhhhhhhhhhhhhhhhhhhhhhhhhhhhhhhhhhhhhhhhhhhhhhhhhhhhhhhhhhhhhhhhhhhhhhhhhhhhhhhhhhhhhhhhhhhhhhhhhhhhhhhhhhhhhhhhhhhhhhhhhhhhhhhhhhhhhhhhhhhhhhhhhhhhhhh
2024-09-14 Schematic notations for rework changes
2024-09-21 Updated schematic in accordance to previous weeks annotated changes
2024-09-28 Added .lck files to .gitignore.
2024-09-28 Renamed Clk to PA5, removed CAN_TX/RX test points, deleted other .lck file and #auto_saved_files# (hopefully this does not break anything.
2024-09-28 Changed testpoints to pin headers.
2024-10-05 removed camera, fixed connectors, and changed status LEDS
2024-10-18 Added back lights + drivers + timer for all blinkers and brake lights
2024-10-19 Fuse added for motorCAN 12V
2024-10-26 Renamed local net labels to be different from hierarchical ones in the MinionBrdInterface so that they aren't connected. Changed Regen input to BPS Hazard light since we aren't using regen but will b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
2024-10-27 Flipped optoisolators, changed resistor values, added second connector to motor can and disconnected shield pins for now since I haven't seen them used (will chack against old version to see what the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
2024-10-27 Changed names and added power flags until KiCAD ERC was satisfied. Hopefully this did not involve doing anything that wasn't supposed to be done.
2024-10-27 Added UTSVT libraries to the gitignore.
2024-10-27 Added footprints. I think this is everything except the fuse.
2024-11-01 Fuse footprint added and blinker changed to software
2024-11-08 Started cleaning some comments, changed EL3H7 data sheet link, removed extra motor CAN connector and changed original one to match (I think) motor controller connector, removed extra mounting holes, 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
2024-11-08 Updated contactor pins.
2024-11-09 added circuitry for limit switch brake, added mosfet to drive LEDs, cleaned up legacy comments, updated resistor values for LEDs
2024-11-09 fixed some footprints and part numbers
2024-11-10 Added/checked datasheet links/part numbers, deleted accel_pot2 and brake_pot2 hierarchical labels and changed corresponding pins (PC2, PC3) to GPIO on the now-2x5 extra GPIO connector.
2024-11-10 Forgot to save, so this might include some changes from the last commit with the deleted potentiometer pins. Also added no-connects to shield pins of motor can.
2024-11-10 Updated ferrite beads.
2024-11-15 added debouncing circuit for limit switch brake
2024-11-15 added pin for limit switch brake on mcu, and fixed hierarchical label
2024-11-16 layout in progress
2024-11-16 routing done for optocouplers
2024-11-17 Shuffled some things closer together.
2024-11-17 Changed EL3H7 footprint from through-hole to SMD.
2024-11-28 fixed routing for optoisolators (might need some spacing), made board a lil smaller, moved clock closer to mc, shuffled some stuff around
2024-11-28 more shuffling things around, re-did edge cuts for new size
2024-11-29 Moved some things inward and squished board, added some labels, broke some traces up (sorry Krish 😣)
2024-11-30 routing is done other than power and usb, DRC is angry bc my goofy routing messed with a lot of the fills
2024-11-30 new pin assignment + routing
2024-12-01 Attempted to finish routing. Also addressed some feedback.
2024-12-07 Added 3A fuse to lights (estimated 9 lights, ~1.8 A plus buffer, changed fuse datasheet to match part number.
2024-12-07 Rerouted PCB - increased 3.3V track width, added cruise indicator lights and lights fuse, fixed DRC thermal relief errors.
2024-12-17 Cleaned up labels a bit.
2024-12-18 More label cleanup.
2024-12-19 Added some graphics.
2024-12-19 fixed a few DRC issues
2024-12-19 Flipped some images.
2024-12-19 Deleted dimension markers.
2024-12-24 Added extra CAN ports for debugging on to schematic.
2024-12-24 Added extra CAN ports to layout.
2025-01-07 Flipped a bunch of connectors so clip is facing inwards
2025-01-07 Flipped CAN Connectors, moved labels to match.
2025-01-07 Made VIso trace for CAN a little bigger.
2025-01-11 Added motor contactor, contactor sense pins, deleted extra GPIO connector 2 since we are now using more of the extra GPIO pins; added new components to layout.
2025-01-11 Switched order of extra ADC pins for easier routing.
2025-01-11 Updated extra gpio footprint to match schematic.
2025-01-11 Did some routing.
2025-01-12 More routing, updated board constraints.
2025-01-12 Improved some fills, added datasheet for CAN chip. About to start moving silkscreen stuff around.
2025-01-12 Fixed a few more unconnected items. Actually going to do silkscreen stuff now.
2025-01-12 Removed some ground traces, put back mcu 3v3 wiring.
2025-01-12 Goodbye last 45-degree angle component.
2025-01-15 Added status LED for motor contactor.
2025-01-15 Changed accel pot resistor values, did some layout aesthetic stuff, started on README.
2025-01-15 More of above, probably.
2025-01-15 Removed vias in small pads.
2025-01-15 Added common libraries as a submodule, updated gitignore and library paths, reconnected item (my bad, sorry about that).
2025-01-16 DRC errors gone whoa
2025-01-16 Moved stuff around a little, added Graphics folder to project library.
2025-01-17 Updated pull request template.
2025-01-17 Updated some symbols to use common libraries (and get rid of warnings.
2025-01-17 Updated pcb to match schematic, deleted second Hallock logo (sorry Dr. Hallock :( )
2025-01-18 Updated comments.
2025-01-18 Replaced unavailable parts
2025-01-18 Filled in part numbers, exported BOM and made Excel file for working with it.
2025-01-18 Added names to board, update BOM.
2025-01-18 generated gerbers (i think?)
2025-01-21 Gerbers in Gerbers folder and zipped Gerbers folder, PDF and PNG of schematic and layout updated.
2025-01-22 Added version update notes.
2025-01-22 Moved version update notes.
2025-02-01 Daybreak rework (#24)
    * Schematic notations for rework changes
    * Updated schematic in accordance to previous weeks annotated changes
    * Added .lck files to .gitignore.
    * Renamed Clk to PA5, removed CAN_TX/RX test points, deleted other .lck file and #auto_saved_files# (hopefully this does not break anything.
    * Changed testpoints to pin headers.
    * removed camera, fixed connectors, and changed status LEDS
2025-02-01 Added 3D models.
2025-04-12 Schematic label fixing.
2025-04-12 Keep project file the same as before.
2025-04-29 Added resistor divider to support 5V potentiometer
2025-04-29 Fixed some silkscreens.
2025-04-29 Fixed silkscreen issues from last version
2025-04-29 Added 3D view and schematic pdf.
2025-05-05 Added pullup resistors to layout; changed the 105R to just 105 on the contactors page because I think that's what it was supposed to be.
2025-05-07 Changed lights to direct drive instead of timer_CLK optoisolator stuff.
2025-05-08 Removed precharge contactor stuff, made accel 5V instead of 3, removed op amp for brake.
2025-05-08 Layout and routing.
2025-05-08 I think the silkscreen is okay now.
2025-05-08 More potentiometer TPs.
2025-05-08 Added part numbers wheeeeeeeeeeeeeeeeeeeee
2025-05-08 BOM for JLCPCB Assemblyyyyy
